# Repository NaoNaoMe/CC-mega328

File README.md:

CC-mega328 Breakout Board
========================================

The CC-mega328 Breakout Board is breakout for the Atmel ATMEGA328P with prototyping area.  
This board shape is dirfferent from Arduino UNO, but it has Arduino Uno V3 style headers.  
There are only the minimal set of parts for running microcontroller. When you make your own circuit boards, this board might be helpful.

### Some highlights of the CC-mega328 Breakout Board:
 1. Main core: [ATMEGA328P](http://www.atmel.com/devices/atmega328p.aspx)
 2. Volatage regulator can be mounted in the extra prototyping area.
 3. Prototyping area 43.94mm(1730mil) x 53.34mm(2100mil)
 4. Measures 99.82mm(3930mil) x 53.34mm(2100mil)

Repository Contents
-------------------
* **/Hardware** - All Eagle design files (.brd, .sch)

Description(Pin Interfaces)
-------------------

### CN1 Pin Descriptions:
This connector is for Flashing a program microcontroller.  
If you change BOOT MODE, To be selected BOOT MODE before connecting the power supply.  
And also, you can Communicate with ATMEGA328P using "Serial" function.
- **VCC:** Restrictly 5.0VDC or 3.3VDC
- **TX:** PD1 used as UART TX.
- **RX:** PD0 used as UART RX.
- **GND:** GND.
- **RESET:** Reset input to microcontroller.
- **EN:** Connected to 3-stete-buffer gate pin H:Enable RESET input L:Disable RESET input(normally)

If you are interested in more useful uart module, please see the [General Serial Communication Board](https://github.com/NaoNaoMe/General-Serial-Communication-Board).

### CN2 Pin Descriptions:
This connector is as power supply.
You can mount a voltage regulator in the extra prototyping area near the connector.
- **VIN:** Depending on the voltage regulator requirements.
- **GND:** GND.

How to burn bootloader and upload sketch
-------------------
See [this page](BurnBootloader.md)

License
-------------------
The repository is released under [Creative Commons ShareAlike 4.0 International](https://creativecommons.org/licenses/by-sa/4.0/).

Distributed as-is; no warranty is given.

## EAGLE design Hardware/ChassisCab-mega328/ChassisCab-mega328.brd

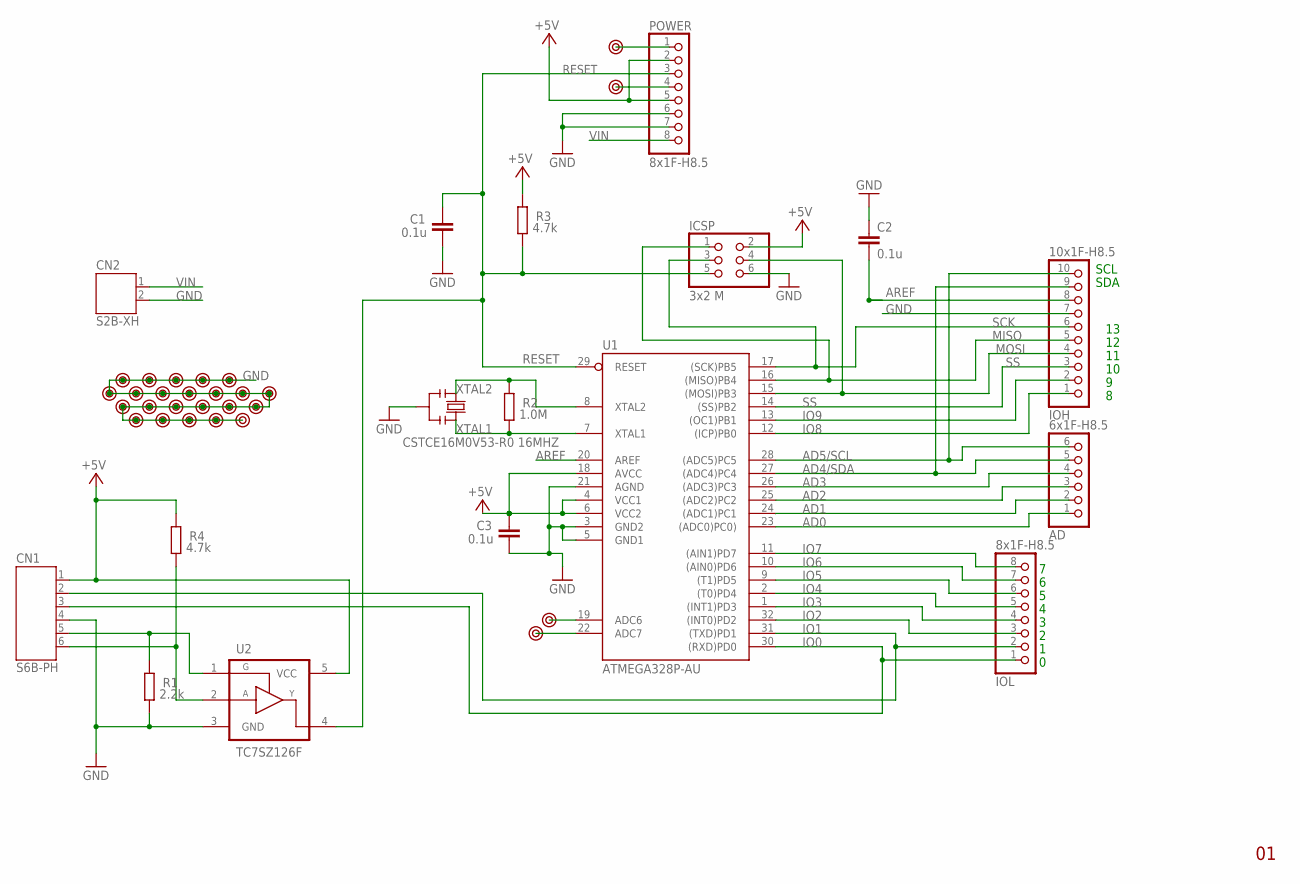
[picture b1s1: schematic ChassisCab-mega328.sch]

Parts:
AD: 6x1F-H8.5; 1X06
C1, C2, C3: 0.1u; C0603
CN1: S6B-PH
CN2: S2B-XH
ICSP: 3x2 M; 2X03
IOH: 10x1F-H8.5; 1X10
IOL: 8x1F-H8.5; 1X08
POWER: 8x1F-H8.5; 1X08
R1: 2.2k; R0603
R2: 1.0M; R0603
R3, R4: 4.7k; R0603
U1: ATMEGA328P-AU; TQFP32
U2: TC7SZ126F; SMV
U$1, U$2, U$3, U$4, U$5, U$6, U$7, U$8, U$9, U$10, U$11, U$12, U$13, U$14, U$15, U$16, U$17, U$18, U$19, U$20, U$21, U$22, U$23, U$24, U$25, U$26, U$27: PAD
X1: CSTCE16M0V53-R0 16MHZ; CSTCE_V

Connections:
+5V: C3.2, CN1.1, ICSP.2, POWER.2, POWER.5, R3.2, R4.2, U1.4 (VCC1), U1.6 (VCC2), U1.18 (AVCC), U2.5 (VCC)
AD0: AD.1, U1.23 ((ADC0)PC0))
AD1: AD.2, U1.24 ((ADC1)PC1)
AD2: AD.3, U1.25 ((ADC2)PC2)
AD3: AD.4, U1.26 ((ADC3)PC3)
AD4/SDA: AD.5, IOH.9, U1.27 ((ADC4)PC4)
AD5/SCL: AD.6, IOH.10, U1.28 ((ADC5)PC5)
AD6: U1.19 (ADC6), U$1.1
AD7: U1.22 (ADC7), U$2.1
AREF: C2.2, IOH.8, U1.20 (AREF)
GND: C1.1, C2.1, C3.1, CN1.4, CN2.2, ICSP.6, IOH.7, POWER.6, POWER.7, R1.1, U1.3 (GND2), U1.5 (GND1), U1.21 (AGND), U2.3 (GND), U$3.1, U$4.1, U$5.1, U$6.1, U$7.1, U$8.1, U$9.1, U$10.1, U$11.1, U$12.1, U$13.1, U$14.1, U$15.1, U$16.1, U$17.1, U$18.1, U$19.1, U$20.1, U$21.1, U$22.1, U$23.1, U$24.1, U$27.1, X1.2
IO0: CN1.3, IOL.1, U1.30 ((RXD)PD0)
IO1: CN1.2, IOL.2, U1.31 ((TXD)PD1)
IO2: IOL.3, U1.32 ((INT0)PD2)
IO3: IOL.4, U1.1 ((INT1)PD3)
IO4: IOL.5, U1.2 ((T0)PD4)
IO5: IOL.6, U1.9 ((T1)PD5)
IO6: IOL.7, U1.10 ((AIN0)PD6)
IO7: IOL.8, U1.11 ((AIN1)PD7)
IO8: IOH.1, U1.12 ((ICP)PB0)
IO9: IOH.2, U1.13 ((OC1)PB1)
MISO: ICSP.1, IOH.5, U1.16 ((MISO)PB4)
MOSI: ICSP.4, IOH.4, U1.15 ((MOSI)PB3)
unnamed: CN1.5, R1.2, U2.1 (G)
unnamed: CN1.6, R4.1, U2.2 (A)
unnamed: POWER.1, U$25.1
unnamed: POWER.4, U$26.1
RESET: C1.2, ICSP.5, POWER.3, R3.1, U1.29 (RESET), U2.4 (Y)
SCK: ICSP.3, IOH.6, U1.17 ((SCK)PB5)
SS: IOH.3, U1.14 ((SS)PB2)
VIN: CN2.1, POWER.8
XTAL1: R2.1, U1.7 (XTAL1), X1.3
XTAL2: R2.2, U1.8 (XTAL2), X1.1

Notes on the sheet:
SDA
SCL

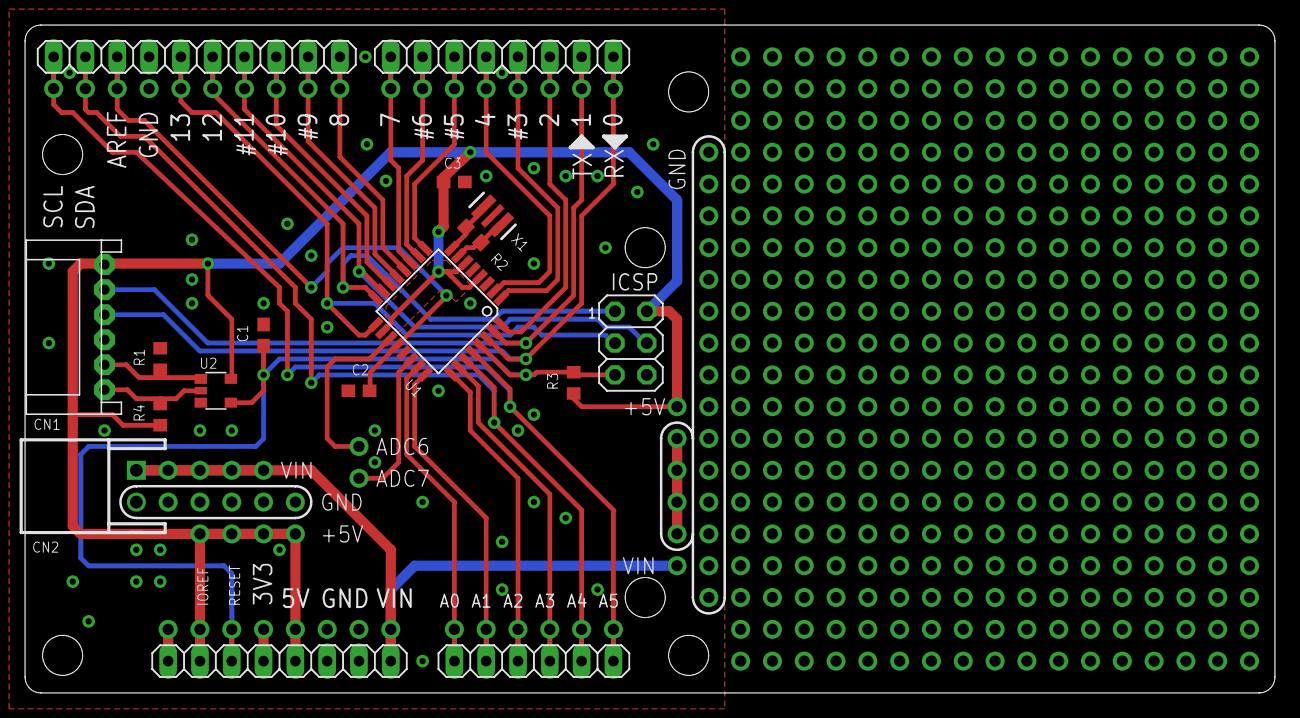
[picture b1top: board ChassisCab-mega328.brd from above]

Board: 2 copper layers, 99.8 x 53.3 mm, 44 parts (0 on the bottom side), 33 nets.

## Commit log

2017-03-31 add files

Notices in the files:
parts and their libraries:
atmel: Copyright (C) 2016, Naoya Imai
